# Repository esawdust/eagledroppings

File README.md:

eagledroppings
==============

Useful utilities from Landon Cox to use with CadSoft Eagle PCB Design Software.
Apache Open Source License.  Landon Cox, elandon at esawdust.com

eagleclone
----------
To start things off, I'm introducing, *eagleclone*, a utility that lets you clone or replicate a 
board and schematic such that it can be imported multiple times into a design without
having to tediously fix-up all the nets, component names, and everything else to create
a new instance of the module within your design.  

The visual explanation: *eagleclone* lets you take a schematic and board layout and clone it as many times 
as you would like.  Using a [Sparkfun OpAmp breakout board](https://www.sparkfun.com/products/9816) as an example 
(Sparkfun design released under Creative Commons), turn a single design:

into multiple instances:

where all you have left is to route the design into the master board design (route airwires.)

For me, I find it easier to layout a board by laying out modules like this first and providing
consistent entry or exit points on the module and cloning when I need multiple instances. 
This approach is more conducive to setting up star wired power routing on a board and even
separate ground planes per instance if need be.

The resulting boards tend to be more consistent. Hand assembling the boards is faster as well
because of consistent placement, but the main thing is design productivity compared to the 
alternatives provided by EAGLE.

This is similar to but a little different than panelizing a design. 
*eagleclone* could be used for panelizing a design allowing you to micro-manage design
placement, but *eagleclone* is really intended to clone fragments to create submodules
that will ultimately be integrated within a larger design.

[Example Usage](#example-usage)

[Use Cases](#use-cases)

[Installation](#installation-on-os-x-or-linux)

Alternative
-----------
In EAGLE, you can copy and paste a design or portion of a design from the schematic view, but
you end up with a pile of parts on the board layout that you have to layout again:

That's clearly not useful. In EAGLE, you can also import a board file to try to make multiple
instances of a layout, but that results in having to rename all the nets and components.
When you import another EAGLE drawing, you have to "Fix up" all the old and new names
manually.  In the case of importing the OpAmp breakout a second time, some of the net names
need to remain the same (power), and some have been changed automatically, and some 
need to be made unique.

This gets you part of the way to a cloned design, but if the original design changes, or you
import the design more than once, you have to go through this process for each instance which is
also not very productive.

Eagleclone deals with this stuff for you, so after you import a clone, there's no re-mapping
of pins and parts to do - *eagleclone* has already renamed everything.

Use Cases
---------
Imagine you're designing a multi-port circuit board, say multi-input amplifier, so you 
start by designing a single channel, schematic, and board layout for that channel. 
Now, you can use *eagleclone* to make as many instances of this design as you want 
where an instance includes both schematic and board layout, but each instance is 
uniquely named so each channel doesn't conflict with the other when you import it into
your master design.
With EAGLE, if you copy and paste the schematic parts, you'd end up with a heap of parts in
the board layout that you would have to layout again.  Alternativley, in the board, 
if you copied your layout, you'd be required to rename all the components and nets. Either
way, EAGLE just doesn't clone sub-systems very well at all. 

Another reason cloning the design like this is nice is if you need to make 
a change to the schematic or board layout, you can do it in the original module, reclone and 
import them.  In other words, with EAGLE, if you have to tediously fix up nets and part names
after importing a design, you're likely not to do it again if you need to change it, so you
either don't change it, or you change it in the derivative work, but not the reusable module,
or you spend a lot of time re-fixing the nets.

But with *eagleclone*, you can simply clone your sch and brd files as many times as needed
and create an 8-port hub without having to interact with EAGLE's net-renaming, component renaming
dialog box for every wire in your design.

This is similar to but a little different than panelizing a design. *eagleclone* is really 
for taking a fragment of a design, say an amplifier design and creating multiple channels
each with its own amplifier instance.  

What is missing from EAGLE (the EAGLE dropping) is the ability to simply copy and paste 
a selected portion of a design in a way that pulls through all the components, nets,
pins, and board layout for that part of the design.

You can import a design into Eagle but if it's the second instance of the design, you're
forced to rename all the components and nets to not conflict with those already there.  This is 
obviously a very tedious and error-prone process and is what *eagleclone* alleviates.

In short, *eagleclone*, creates multiple instances of a particular layout so you don't 
have to re-layout the same module multiple times or fuss with renaming through the EAGLE
import dialog box.

Since version 6 of EAGLE, the board (.brd) and schematic (.sch) files have been stored in
XML format.  This utility assumes you have EAGLE 6 XML design files.

Prerequisites are: 
1) Ruby 2.0.0 
2) EAGLE 6.x .brd and .sch EAGLE file of the design you want to replicate.  
3) Nokogiri

Example Usage
-------------

```bash
$ ./eagleclone.rb --help

Usage: *eagleclone* -d design_to_clone -p clone_postfix
    -d, --design DESIGN              specify design file without file extension
    -p, --postfix POSTFIX            specify the postfix to append to all parts, signals, etc
    -h, --help                       Show this message

```
Assume you have an EAGLE design called 'test' and the two EAGLE files are 'test.brd' and 'test.sch'
for PCB board and schematic, respectively.  You can create new three new instances of this design 
called A, B, and C, as follows:

```bash
$ ./*eagleclone*.rb -d test -p A
$ ./*eagleclone*.rb -d test -p B
$ ./*eagleclone*.rb -d test -p C
```
This creates three new instances of the test design that are 'A', 'B', and 'C' instances of the original design:
```bash
testA.brd
testA.sch
testB.brd
testB.sch
testC.brd
testC.sch
```

The files are created in the same directory in which the original design exists.  The original design
is never modified and *eagleclone* is idempotent (it will overwrite any files previously generated by
*eagleclone*.) At this stage, you have three new designs, each uniquely named 

To use these replicated designs:

1) In EAGLE, you would load up the master design into which you want to import these instances, then
switch to the board layout view of that design. 

2) File->Import each of the .brd files above for A, B, and C respectively
2a) When you import a design it lets you place it somewhere on your board layout much as if 
you were placing a component on the board, but you can place the entire imported design instead.
2b) Notice that when you import the .brd clone, its schematic comes right along with it as a 
new sheet in your design which is nice to keep the instances all separated and easy to manage 
within EAGLE.

3) Route your board normally from there.  It's useful to provide some connection points on 
your sub-module in the board layout before you clone it - just makes it somewhat easier to 
treat each module like a self-contained layout you just need to hook up to the rest of your design.

How it works
------------

*eagleclone* uses Nokogiri, a Ruby gem which knows how to read and write XML files, to ingest the
EAGLE board and schematic files.  Then using XPath queries, it identifies all the nodes in the XML
files which need to be renamed or replaced with new instance names derived from the original name plus
the instance parameter given by the -p option on the command line.

It then replaces the names and writes out a corresponding .sch and .brd file that has the new 
instance information in it.  The new file is effectively a completely independent design.

Caveats
-------
*eagleclone* looks for certain power supply-related signals such as 3.3V, 5.0V, VCC, VDD, and 
GND and does not replace those.  

It's assumed each design derived from the original will use the same power and ground signals
as the original design.  This makes the instances easier to import and requires no fixup after import.

Installation on OS X or Linux
------------------------------

Prerequisites are simply Ruby 2.0 and the Gems specified in the gemfile.
Currently developed and tested on OS X and Linux.  Should work
under Cygwin on Windows, but not tested.

The easiest way to install ruby is to use RVM:  https://rvm.io
```bash
$ \curl -L https://get.rvm.io | bash -s stable
$ source ~/.profile
$ rvm install 2.0.0
```

Pull the eagledroppings directory from github to install the source:
```bash
$ cd <your install directory>
$ git clone git@github.com:esawdust/eagledroppings.git
```

Then from the directory in which you installed *eagleclone*, install the requisite gems
for *eagleclone*:

```bash
*eagleclone* $ bundle install
```
to install the prerequisite gems.

RSpec tests have been provided if you want to run those to insure you have everything 
installed correctly and the *eagleclone* utility is working properly.

Run rspec by itself on the command line and the tests will run.  If you see '0 failures'
you know you're good to go.

```bash
eagleclone $ rspec
....................

Finished in 0.48173 seconds
20 examples, 0 failures
```

TODO
----
1) Make *eagleclone* a gem.
2) Add feature to clone one design multiple times into one file (vs one file per clone.)

Apache Open Source License
--------------------------
Copyright 2013 Landon Cox

   Licensed under the Apache License, Version 2.0 (the "License");
   you may not use this file except in compliance with the License.
   You may obtain a copy of the License at

       http://www.apache.org/licenses/LICENSE-2.0

   Unless required by applicable law or agreed to in writing, software
   distributed under the License is distributed on an "AS IS" BASIS,
   WITHOUT WARRANTIES OR CONDITIONS OF ANY KIND, either express or implied.
   See the License for the specific language governing permissions and
   limitations under the License.

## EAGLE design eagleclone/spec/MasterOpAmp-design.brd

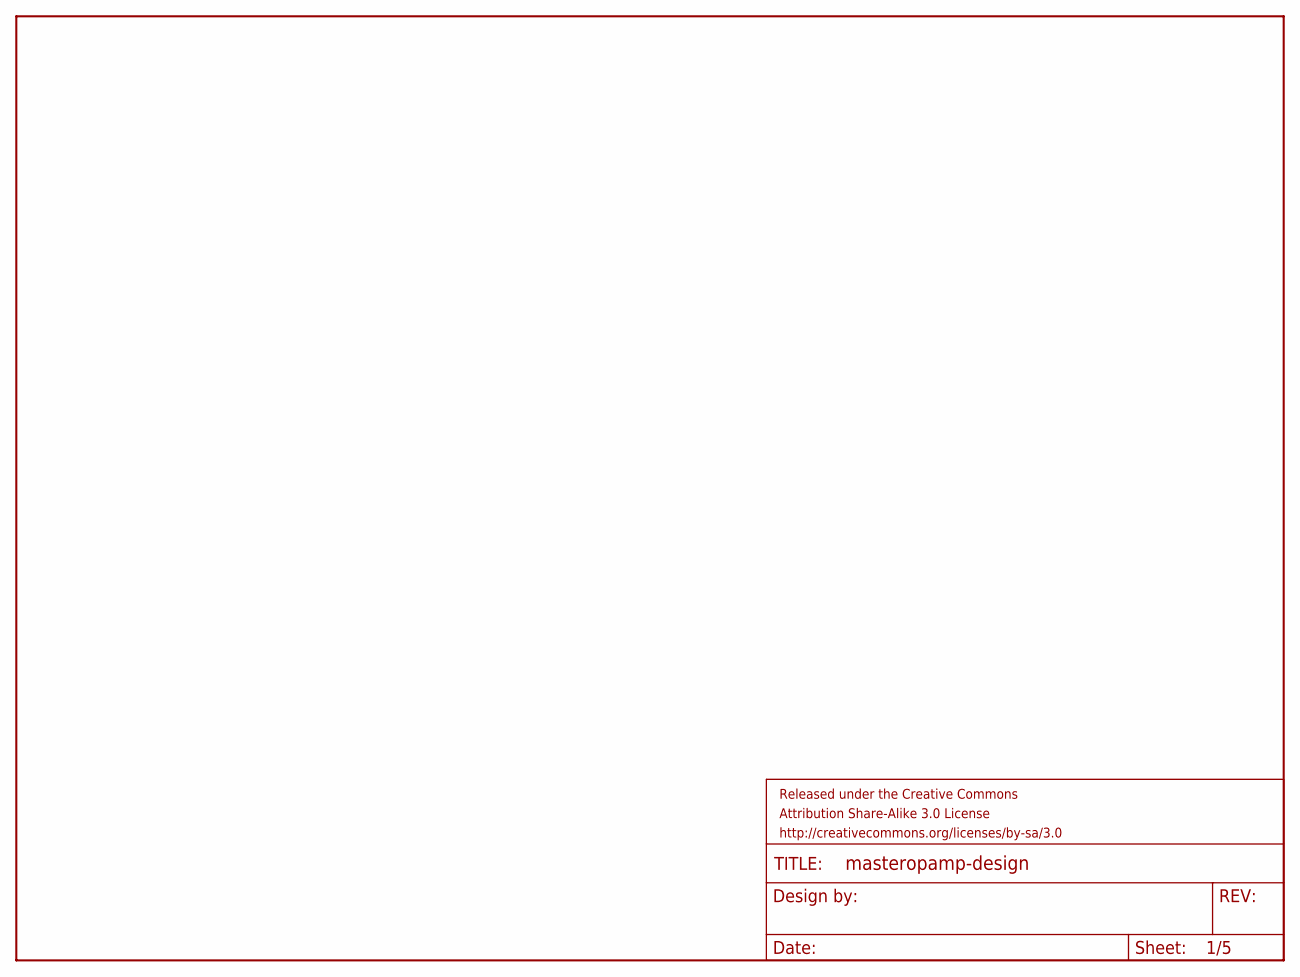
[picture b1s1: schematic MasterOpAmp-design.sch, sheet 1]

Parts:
FRAME1: FRAME-LETTER; CREATIVE_COMMONS

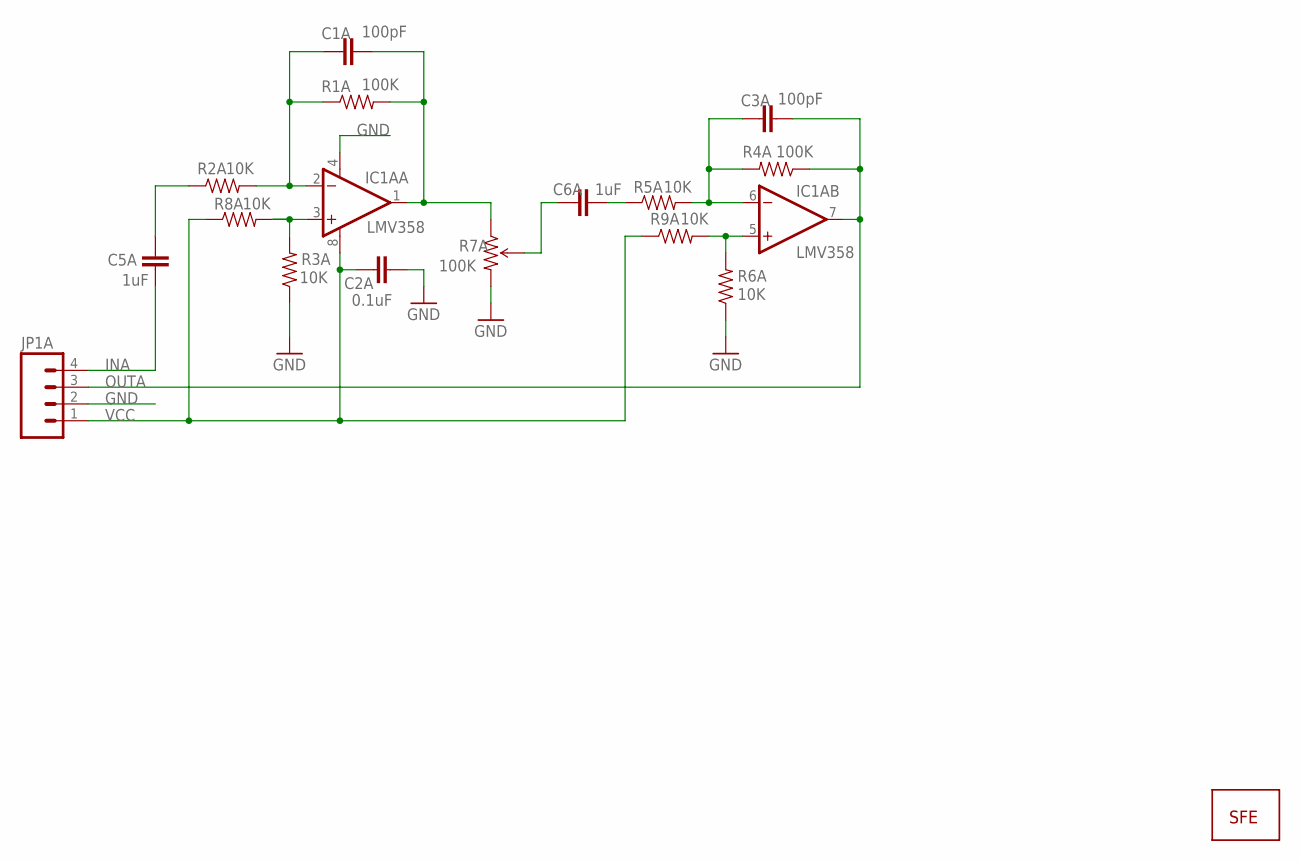
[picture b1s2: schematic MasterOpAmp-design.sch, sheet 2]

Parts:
C1A, C3A: 100pF; C0402
C2A: 0.1uF; C0402
C5A, C6A: 1uF; C0402
IC1A: LMV358; SO08
JP1A: M04PTH; 1X04
R1A, R4A: 100K; C0402
R2A, R3A, R5A, R6A, R8A, R9A: 10K; C0402
R7A: 100K; TRIMPOT-3MM
U$3A: LOGO-SFENEW; SFE-NEW-WEBLOGO

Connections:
GND: C2A.2, IC1A.4 (V-), JP1A.2, R3A.1, R6A.1, R7A.3 (CW); also elsewhere on the board
IN1A: C5A.2, R2A.1
INA: C5A.1, JP1A.4
unnamed: IC1A.5 (+IN), R6A.2, R9A.2
unnamed: C1A.1, IC1A.2 (-IN), R1A.1, R2A.2
unnamed: IC1A.3 (+IN), R3A.2, R8A.2
unnamed: C6A.1, R5A.1
unnamed: C6A.2, R7A.2 (WIPER)
unnamed: C3A.1, IC1A.6 (-IN), R4A.2, R5A.2
OUT1A: C1A.2, IC1A.1 (OUT), R1A.2, R7A.1 (CCW)
OUTA: C3A.2, IC1A.7 (OUT), JP1A.3, R4A.1
VCC: C2A.1, IC1A.8 (V+), JP1A.1, R8A.1, R9A.1; also elsewhere on the board

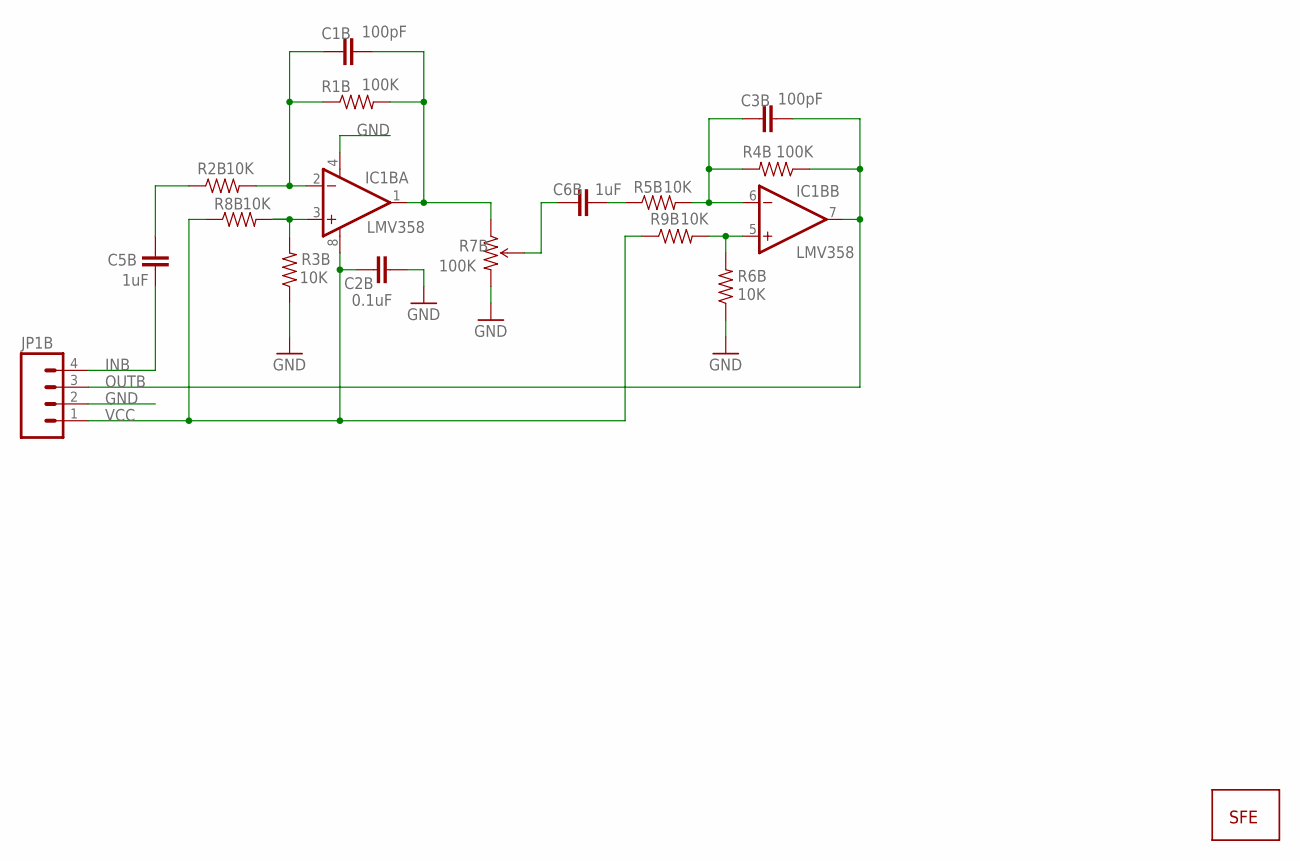
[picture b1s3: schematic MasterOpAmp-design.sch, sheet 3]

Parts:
C1B, C3B: 100pF; C0402
C2B: 0.1uF; C0402
C5B, C6B: 1uF; C0402
IC1B: LMV358; SO08
JP1B: M04PTH; 1X04
R1B, R4B: 100K; C0402
R2B, R3B, R5B, R6B, R8B, R9B: 10K; C0402
R7B: 100K; TRIMPOT-3MM
U$3B: LOGO-SFENEW; SFE-NEW-WEBLOGO

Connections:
GND: C2B.2, IC1B.4 (V-), JP1B.2, R3B.1, R6B.1, R7B.3 (CW); also elsewhere on the board
IN1B: C5B.2, R2B.1
INB: C5B.1, JP1B.4
unnamed: IC1B.5 (+IN), R6B.2, R9B.2
unnamed: C1B.1, IC1B.2 (-IN), R1B.1, R2B.2
unnamed: IC1B.3 (+IN), R3B.2, R8B.2
unnamed: C6B.1, R5B.1
unnamed: C6B.2, R7B.2 (WIPER)
unnamed: C3B.1, IC1B.6 (-IN), R4B.2, R5B.2
OUT1B: C1B.2, IC1B.1 (OUT), R1B.2, R7B.1 (CCW)
OUTB: C3B.2, IC1B.7 (OUT), JP1B.3, R4B.1
VCC: C2B.1, IC1B.8 (V+), JP1B.1, R8B.1, R9B.1; also elsewhere on the board

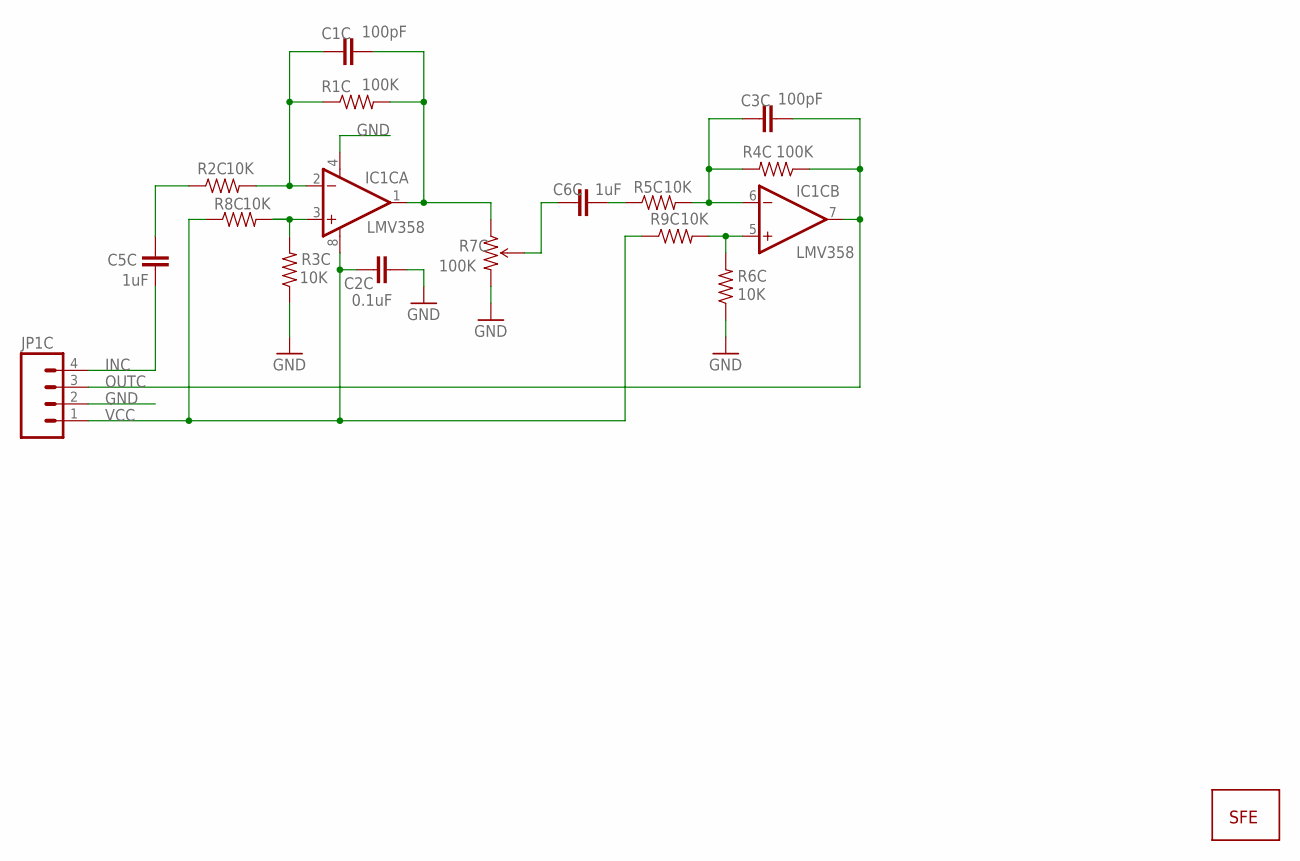
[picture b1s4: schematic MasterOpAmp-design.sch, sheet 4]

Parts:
C1C, C3C: 100pF; C0402
C2C: 0.1uF; C0402
C5C, C6C: 1uF; C0402
IC1C: LMV358; SO08
JP1C: M04PTH; 1X04
R1C, R4C: 100K; C0402
R2C, R3C, R5C, R6C, R8C, R9C: 10K; C0402
R7C: 100K; TRIMPOT-3MM
U$3C: LOGO-SFENEW; SFE-NEW-WEBLOGO

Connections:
GND: C2C.2, IC1C.4 (V-), JP1C.2, R3C.1, R6C.1, R7C.3 (CW); also elsewhere on the board
IN1C: C5C.2, R2C.1
INC: C5C.1, JP1C.4
unnamed: IC1C.5 (+IN), R6C.2, R9C.2
unnamed: C1C.1, IC1C.2 (-IN), R1C.1, R2C.2
unnamed: IC1C.3 (+IN), R3C.2, R8C.2
unnamed: C6C.1, R5C.1
unnamed: C6C.2, R7C.2 (WIPER)
unnamed: C3C.1, IC1C.6 (-IN), R4C.2, R5C.2
OUT1C: C1C.2, IC1C.1 (OUT), R1C.2, R7C.1 (CCW)
OUTC: C3C.2, IC1C.7 (OUT), JP1C.3, R4C.1
VCC: C2C.1, IC1C.8 (V+), JP1C.1, R8C.1, R9C.1; also elsewhere on the board

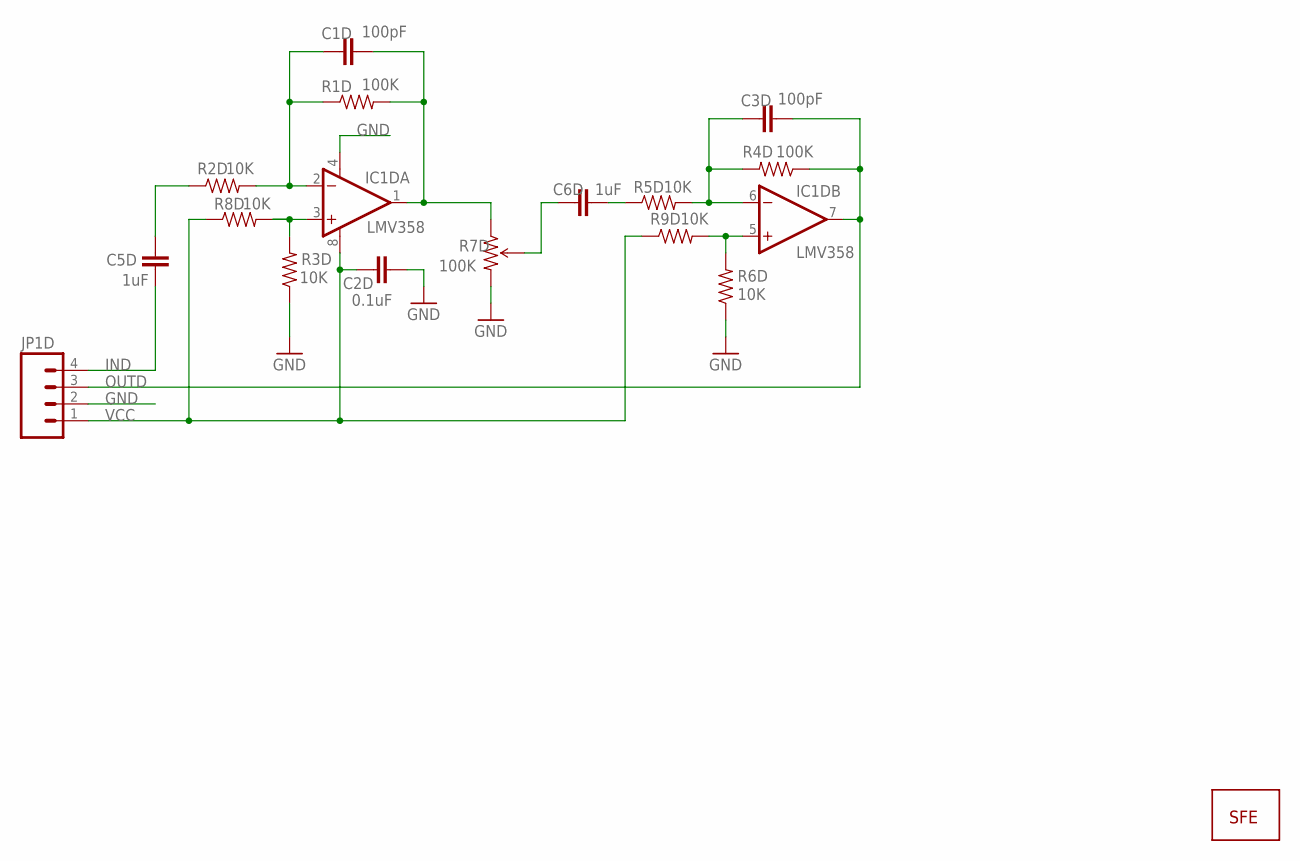
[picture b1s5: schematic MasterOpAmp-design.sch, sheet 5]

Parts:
C1D, C3D: 100pF; C0402
C2D: 0.1uF; C0402
C5D, C6D: 1uF; C0402
IC1D: LMV358; SO08
JP1D: M04PTH; 1X04
R1D, R4D: 100K; C0402
R2D, R3D, R5D, R6D, R8D, R9D: 10K; C0402
R7D: 100K; TRIMPOT-3MM
U$3D: LOGO-SFENEW; SFE-NEW-WEBLOGO

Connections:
GND: C2D.2, IC1D.4 (V-), JP1D.2, R3D.1, R6D.1, R7D.3 (CW); also elsewhere on the board
IN1D: C5D.2, R2D.1
IND: C5D.1, JP1D.4
unnamed: IC1D.5 (+IN), R6D.2, R9D.2
unnamed: C1D.1, IC1D.2 (-IN), R1D.1, R2D.2
unnamed: IC1D.3 (+IN), R3D.2, R8D.2
unnamed: C6D.1, R5D.1
unnamed: C6D.2, R7D.2 (WIPER)
unnamed: C3D.1, IC1D.6 (-IN), R4D.2, R5D.2
OUT1D: C1D.2, IC1D.1 (OUT), R1D.2, R7D.1 (CCW)
OUTD: C3D.2, IC1D.7 (OUT), JP1D.3, R4D.1
VCC: C2D.1, IC1D.8 (V+), JP1D.1, R8D.1, R9D.1; also elsewhere on the board

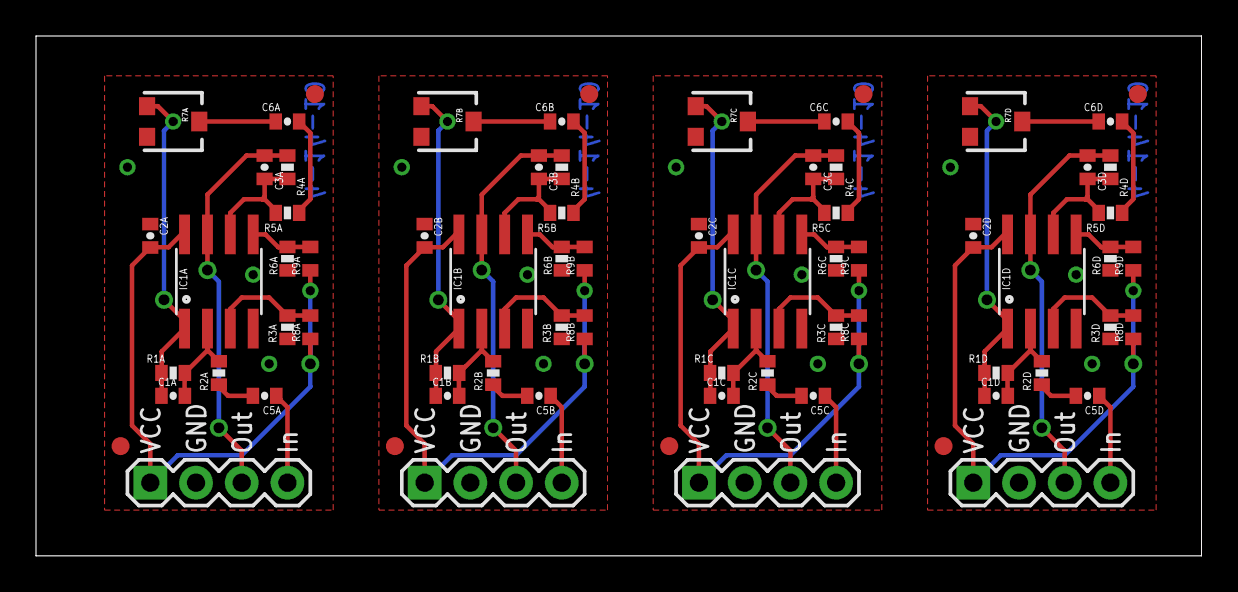
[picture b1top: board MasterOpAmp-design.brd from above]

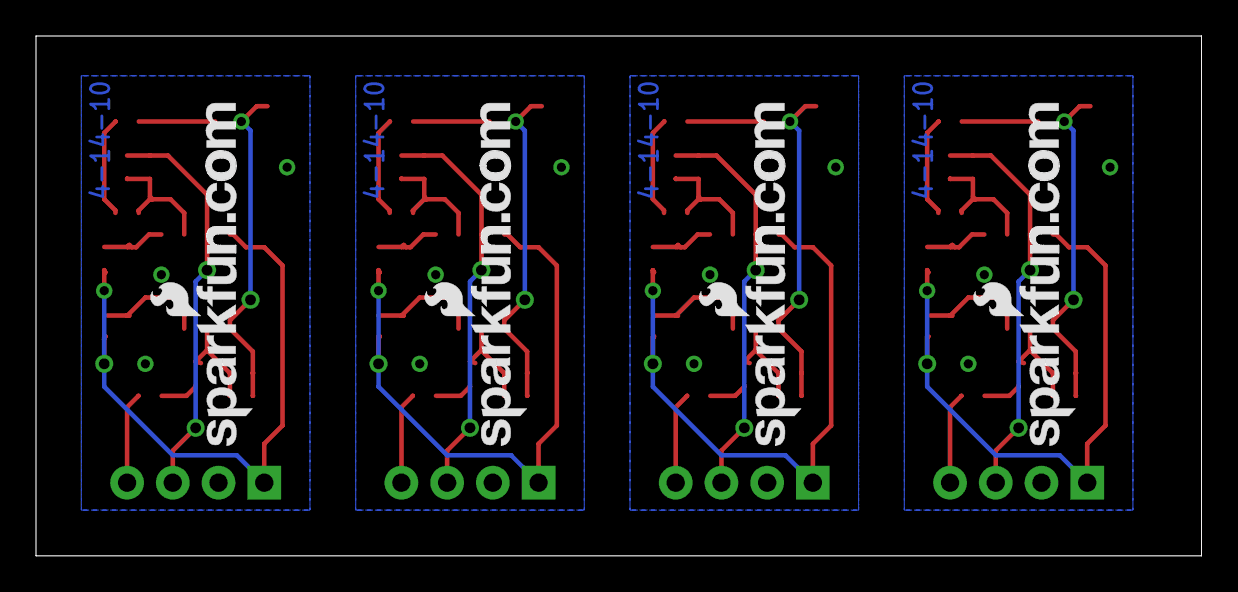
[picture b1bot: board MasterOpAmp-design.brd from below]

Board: 2 copper layers, 64.8 x 28.9 mm, 77 parts (4 on the bottom side), 42 nets.

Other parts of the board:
E$1A, E$1B, E$1C, E$1D, E$2A, E$2B, E$2C, E$2D: FIDUCIAL-1X2

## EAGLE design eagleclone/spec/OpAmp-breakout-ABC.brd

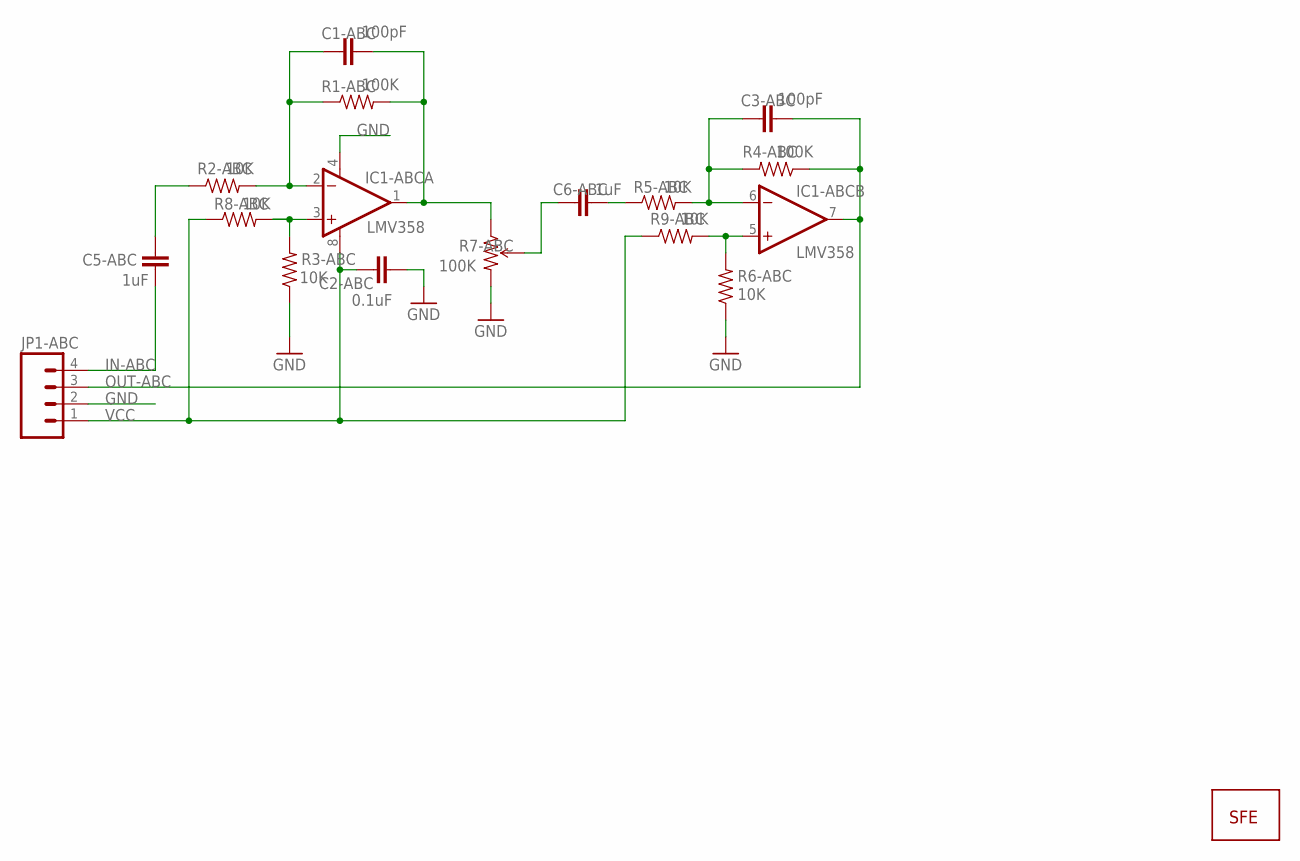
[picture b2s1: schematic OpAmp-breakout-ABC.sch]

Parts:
C1-ABC, C3-ABC: 100pF; C0402
C2-ABC: 0.1uF; C0402
C5-ABC, C6-ABC: 1uF; C0402
IC1-ABC: LMV358; SO08
JP1-ABC: M04PTH; 1X04
R1-ABC, R4-ABC: 100K; C0402
R2-ABC, R3-ABC, R5-ABC, R6-ABC, R8-ABC, R9-ABC: 10K; C0402
R7-ABC: 100K; TRIMPOT-3MM
U$3-ABC: LOGO-SFENEW; SFE-NEW-WEBLOGO

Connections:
GND: C2-ABC.2, IC1-ABC.4 (V-), JP1-ABC.2, R3-ABC.1, R6-ABC.1, R7-ABC.3 (CW)
IN1-ABC: C5-ABC.2, R2-ABC.1
IN-ABC: C5-ABC.1, JP1-ABC.4
unnamed: IC1-ABC.5 (+IN), R6-ABC.2, R9-ABC.2
unnamed: C1-ABC.1, IC1-ABC.2 (-IN), R1-ABC.1, R2-ABC.2
unnamed: IC1-ABC.3 (+IN), R3-ABC.2, R8-ABC.2
unnamed: C6-ABC.1, R5-ABC.1
unnamed: C6-ABC.2, R7-ABC.2 (WIPER)
unnamed: C3-ABC.1, IC1-ABC.6 (-IN), R4-ABC.2, R5-ABC.2
OUT1-ABC: C1-ABC.2, IC1-ABC.1 (OUT), R1-ABC.2, R7-ABC.1 (CCW)
OUT-ABC: C3-ABC.2, IC1-ABC.7 (OUT), JP1-ABC.3, R4-ABC.1
VCC: C2-ABC.1, IC1-ABC.8 (V+), JP1-ABC.1, R8-ABC.1, R9-ABC.1

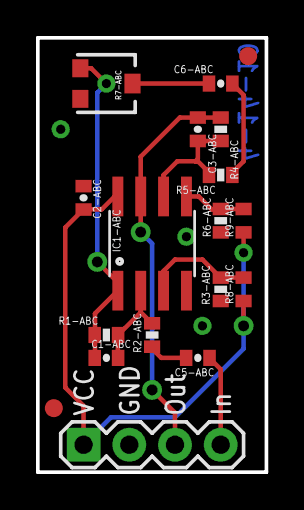
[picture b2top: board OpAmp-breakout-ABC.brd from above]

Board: 2 copper layers, 12.7 x 24.1 mm, 19 parts (1 on the bottom side), 12 nets.

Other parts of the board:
E$1-ABC, E$2-ABC: FIDUCIAL-1X2

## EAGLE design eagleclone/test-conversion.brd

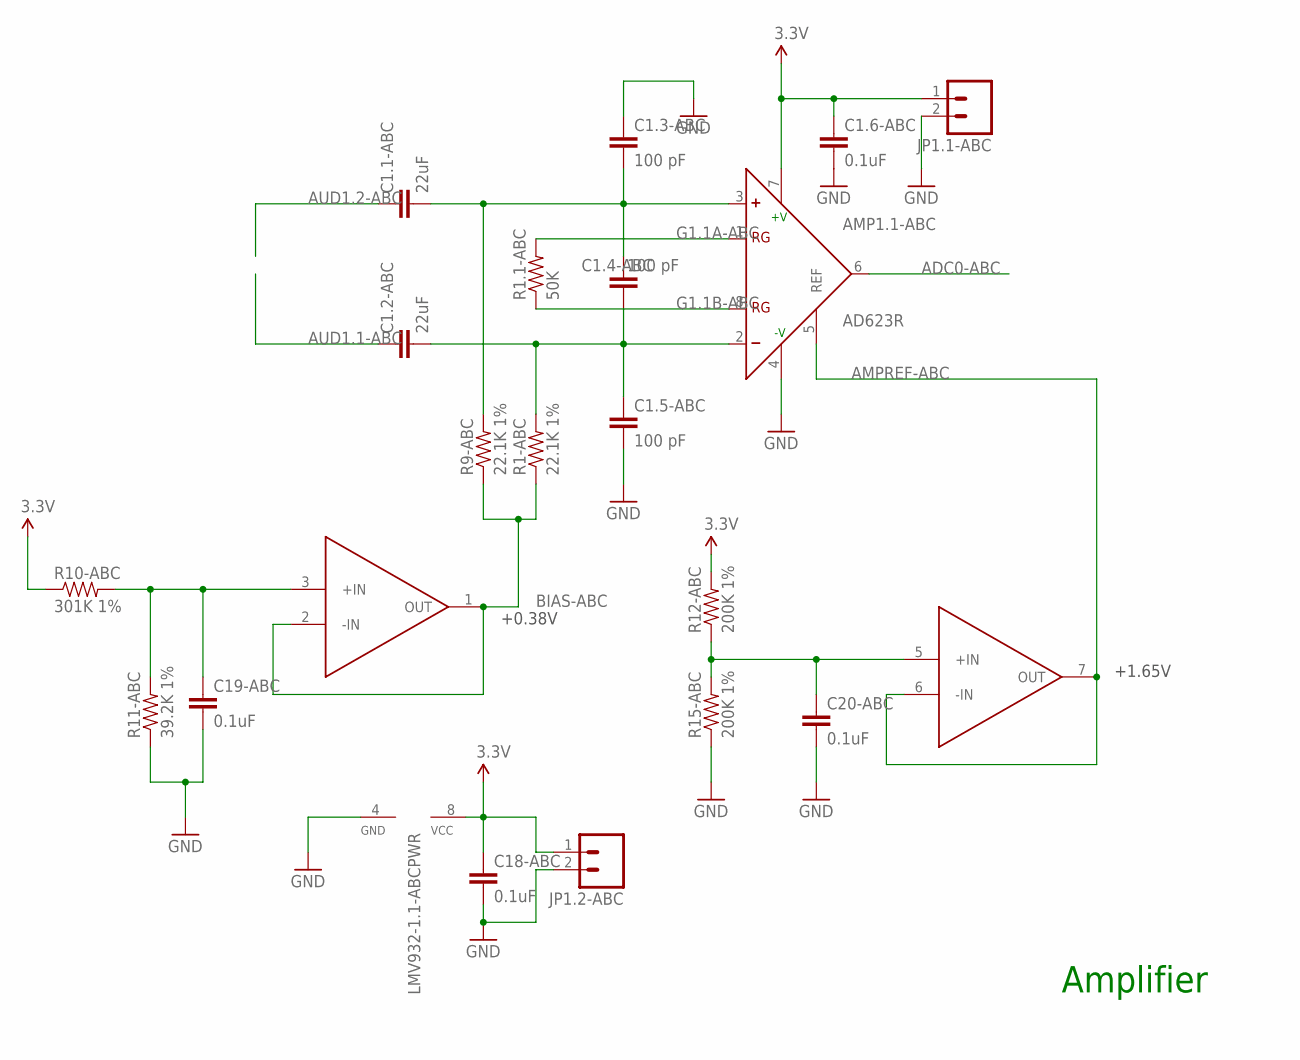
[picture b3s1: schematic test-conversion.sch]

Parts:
AMP1.1-ABC: AD623R; SO8; DIGIKEY AD623ARZ-ND
C1.1-ABC, C1.2-ABC: 22uF; 1206; DIGIKEY 399-3229-1-ND
C1.3-ABC, C1.4-ABC, C1.5-ABC: 100 pF; 0805
C1.6-ABC, C18-ABC, C19-ABC, C20-ABC: 0.1uF; 0805
JP1.1-ABC, JP1.2-ABC: M021X02_NO_SILK; 1X02_NO_SILK
LMV932-1.1-ABC: LMV932; SOIC8
R1-ABC, R9-ABC: 22.1K 1%; 0805
R1.1-ABC: 50K; 0805
R10-ABC: 301K 1%; 0805
R11-ABC: 39.2K 1%; 0805
R12-ABC, R15-ABC: 200K 1%; 0805

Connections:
3.3V: AMP1.1-ABC.7 (+V), C1.6-ABC.1, C18-ABC.1, JP1.1-ABC.1, JP1.2-ABC.1, LMV932-1.1-ABC.8 (VCC), R10-ABC.1, R12-ABC.2
ADC0-ABC: AMP1.1-ABC.6 (OUT)
AMPREF-ABC: AMP1.1-ABC.5 (REF), LMV932-1.1-ABC.6 (-IN), LMV932-1.1-ABC.7 (OUT)
AUD1.1-ABC: C1.2-ABC.1
AUD1.2-ABC: C1.1-ABC.1
BIAS-ABC: LMV932-1.1-ABC.1 (OUT), LMV932-1.1-ABC.2 (-IN), R1-ABC.1, R9-ABC.1
G1.1A-ABC: AMP1.1-ABC.1 (RG), R1.1-ABC.2
G1.1B-ABC: AMP1.1-ABC.8 (RG), R1.1-ABC.1
GND: AMP1.1-ABC.4 (-V), C1.3-ABC.1, C1.5-ABC.2, C1.6-ABC.2, C18-ABC.2, C19-ABC.2, C20-ABC.2, JP1.1-ABC.2, JP1.2-ABC.2, LMV932-1.1-ABC.4 (GND), R11-ABC.1, R15-ABC.1
unnamed: AMP1.1-ABC.2 (-), C1.2-ABC.2, C1.4-ABC.2, C1.5-ABC.1, R1-ABC.2
unnamed: AMP1.1-ABC.3 (+), C1.1-ABC.2, C1.3-ABC.2, C1.4-ABC.1, R9-ABC.2
unnamed: C19-ABC.1, LMV932-1.1-ABC.3 (+IN), R10-ABC.2, R11-ABC.2
unnamed: C20-ABC.1, LMV932-1.1-ABC.5 (+IN), R12-ABC.1, R15-ABC.2

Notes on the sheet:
Amplifier
+0.38V
+1.65V

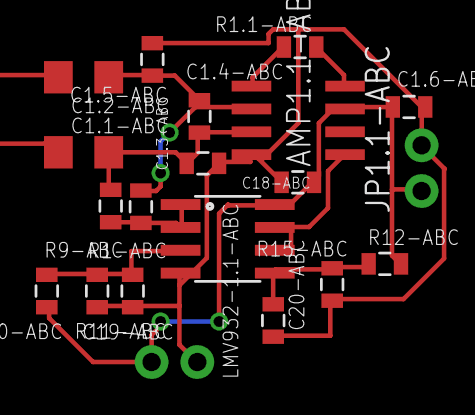
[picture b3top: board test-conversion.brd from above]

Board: 2 copper layers, 20 parts (0 on the bottom side), 10 nets.

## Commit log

2013-10-09 initial checkin
2013-10-09 added apache 2.0 license
2013-10-09 adding documentation
2013-10-09 documentation editing
2013-10-11 added CC design for demo and test
2013-10-11 readme changes
2013-10-11 naming refactoring
2013-10-11 refactoring, added .rspec so could run all specs at once, moved test data into spec dir
2013-10-11 refactoring code and tests, need to replace all respec test criteria with counts and names coming from the Sparkfun OpAmp breakout board
2013-10-11 latest tests using the Sparkfun OpAmp breakout board as test subject
2013-10-11 added some more of the common power names so they don't get translated
2013-10-13 doc edits
2013-10-14 getting tutorial ready to go
2013-10-14 refactoring image names
2013-10-15 latest docs
2013-10-15 working on incorporating images into github markdown
2013-10-15 working on markdown for images
2013-10-15 latest documentation and screenshots
2013-10-15 tweaking docs

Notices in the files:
parts and their libraries:
SparkFun-Aesthetics: Licensing: CC v3.0 Share-Alike You are welcome to use this library for commercial purposes.
SparkFun-Aesthetics: Released under the Creative Commons Attribution Share-Alike 3.0 License
SparkFun-Aesthetics: http://creativecommons.org/licenses/by-sa/3.0
